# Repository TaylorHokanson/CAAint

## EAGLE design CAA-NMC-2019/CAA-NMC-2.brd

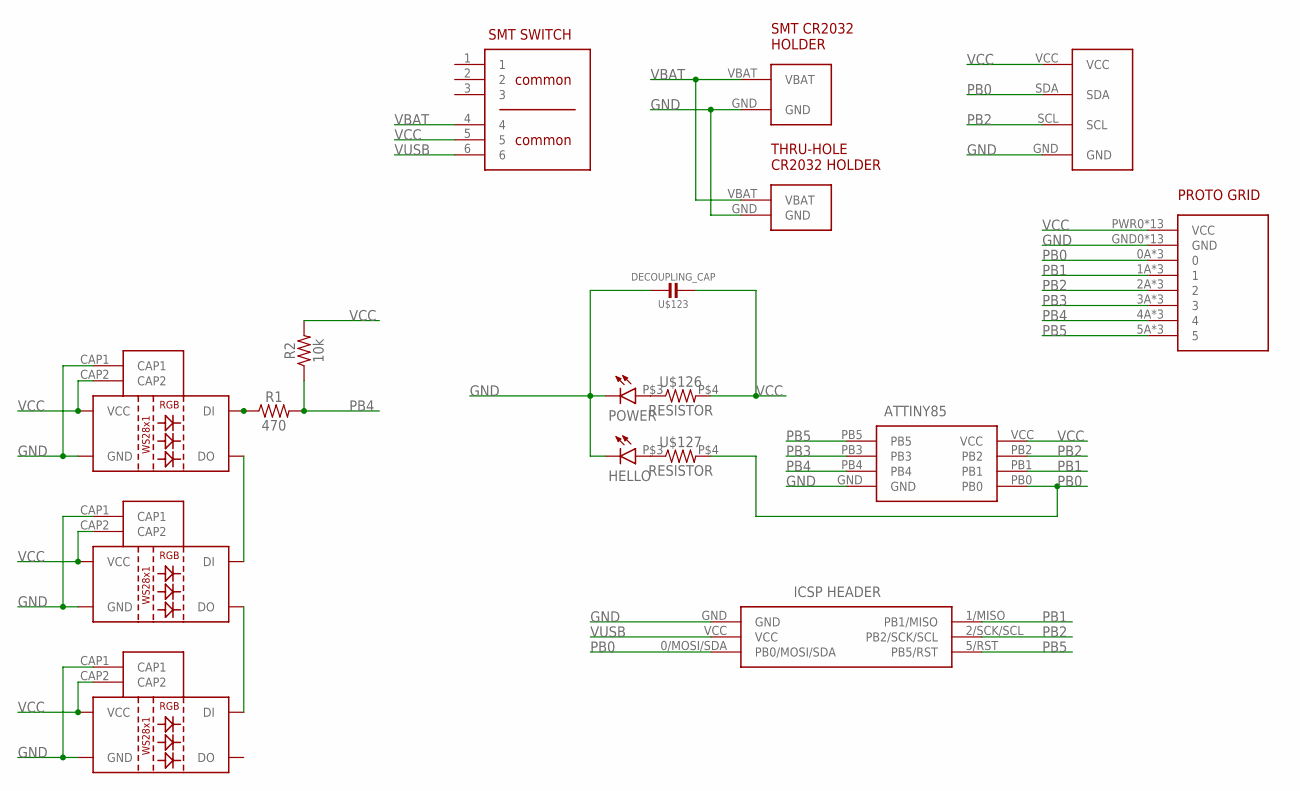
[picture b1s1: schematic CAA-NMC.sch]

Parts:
D1, D2, D3: WS2812B
HELLO: LED3MM
IC1: ATTINY85-20SU; SOT127P798X216-8N
J1: M20-9980346; HDRV6W64P254_2X3_762X508X868P
POWER: LED3MM
R1: 470; 0603
R2: 10k; 0603
U$1: PROTO
U$2: SMT-BATTERY-HOLDER; SMT-CR-HOLDER
U$3: THRU-CR-HOLDER
U$4: I2C-PADS
U$123: DECOUPLING_CAP
U$126, U$127: RESISTOR; AXIAL-0.3
U$145: SMT-SWITCH

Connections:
GND: D1.CAP1, D1.GND, D2.CAP1, D2.GND, D3.CAP1, D3.GND, HELLO.NEG, IC1.GND, J1.GND, POWER.NEG, U$1.GND0 (GND), U$1.GND1 (GND), U$1.GND2 (GND), U$1.GND3 (GND), U$1.GND4 (GND), U$1.GND5 (GND), U$1.GND6 (GND), U$1.GND7 (GND), U$1.GND8 (GND), U$1.GND9 (GND), U$1.GND10 (GND), U$1.GND11 (GND), U$1.GND12 (GND), U$2.GND, U$3.GND, U$4.GND, U$123.P$1 (1)
unnamed: POWER.POS, U$126.P$3 (1)
unnamed: HELLO.POS, U$127.P$3 (1)
unnamed: D1.DO, D2.DI
unnamed: D2.DO, D3.DI
unnamed: D1.DI, R1.1
PB0: IC1.PB0, J1.0/MOSI/SDA (PB0/MOSI/SDA), U$1.0A (0), U$1.0B (0), U$1.0C (0), U$4.SDA, U$127.P$4 (2)
PB1: IC1.PB1, J1.1/MISO (PB1/MISO), U$1.1A (1), U$1.1B (1), U$1.1C (1)
PB2: IC1.PB2, J1.2/SCK/SCL (PB2/SCK/SCL), U$1.2A (2), U$1.2B (2), U$1.2C (2), U$4.SCL
PB3: IC1.PB3, U$1.3A (3), U$1.3B (3), U$1.3C (3)
PB4: IC1.PB4, R1.2, R2.1, U$1.4A (4), U$1.4B (4), U$1.4C (4)
PB5: IC1.PB5, J1.5/RST (PB5/RST), U$1.5A (5), U$1.5B (5), U$1.5C (5)
VBAT: U$2.VBAT, U$3.VBAT, U$145.4
VCC: D1.CAP2, D1.VCC, D2.CAP2, D2.VCC, D3.CAP2, D3.VCC, IC1.VCC, R2.2, U$1.PWR0 (VCC), U$1.PWR1 (VCC), U$1.PWR2 (VCC), U$1.PWR3 (VCC), U$1.PWR4 (VCC), U$1.PWR5 (VCC), U$1.PWR6 (VCC), U$1.PWR7 (VCC), U$1.PWR8 (VCC), U$1.PWR9 (VCC), U$1.PWR10 (VCC), U$1.PWR11 (VCC), U$1.PWR12 (VCC), U$4.VCC, U$123.P$2 (2), U$126.P$4 (2), U$145.5
VUSB: J1.VCC, U$145.6

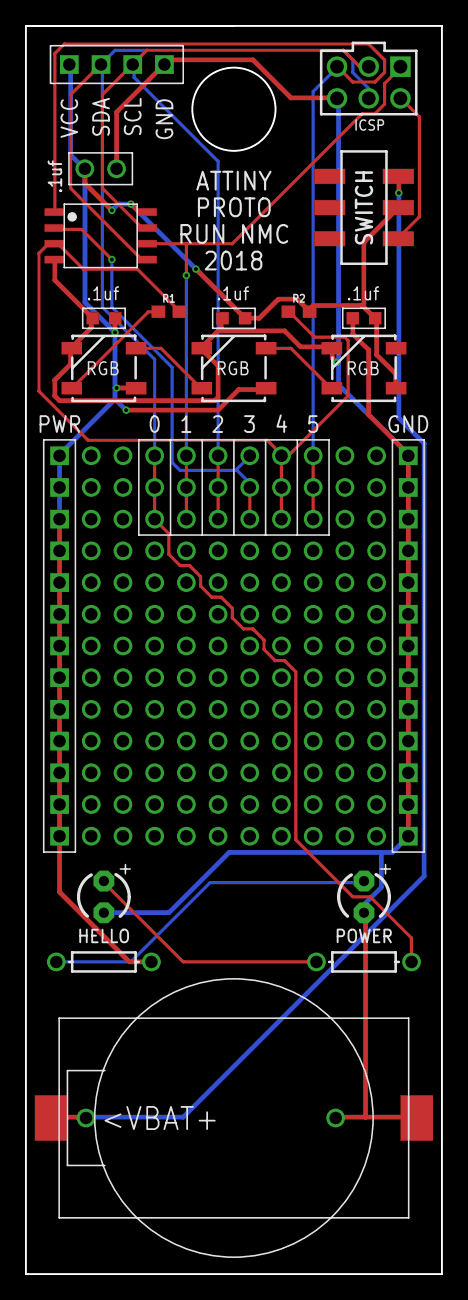
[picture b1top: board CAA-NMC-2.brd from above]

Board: 2 copper layers, 33.3 x 100.0 mm, 17 parts (0 on the bottom side), 15 nets.

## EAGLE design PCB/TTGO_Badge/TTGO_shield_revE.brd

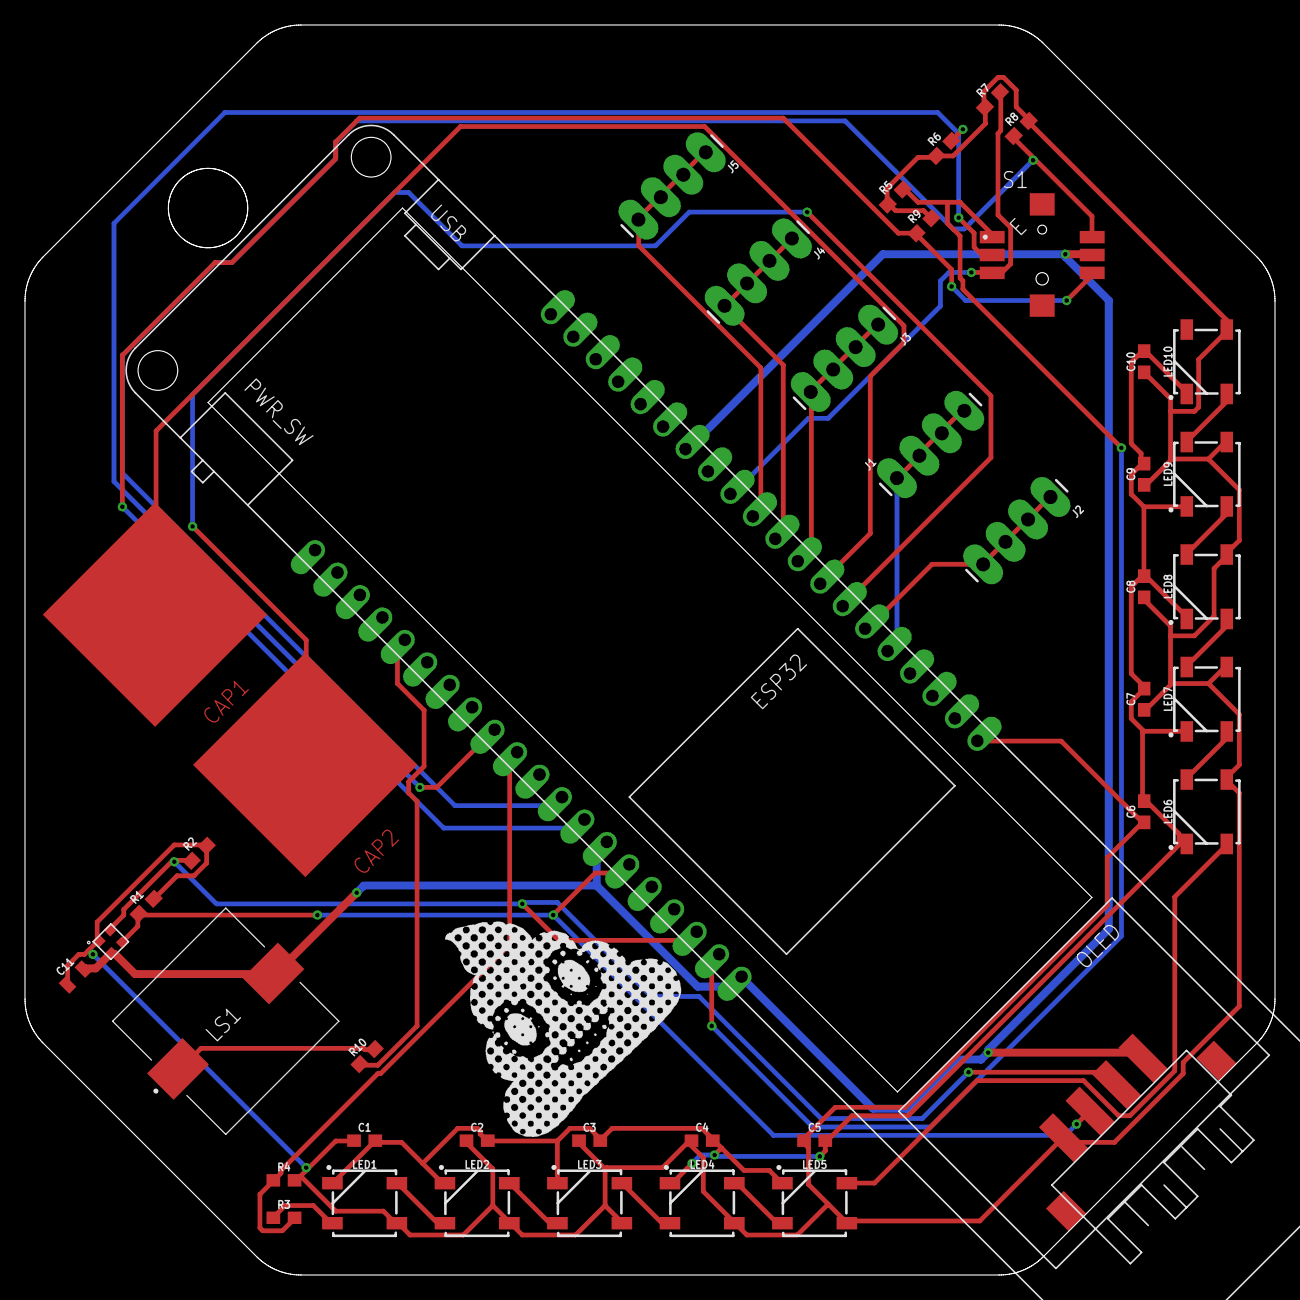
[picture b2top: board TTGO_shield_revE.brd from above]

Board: 2 copper layers, 100.0 x 100.0 mm, 43 parts (0 on the bottom side), 30 nets.

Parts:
C1, C2, C3, C4, C5, C6, C7, C8, C9, C10: 0.1uF; 0603
C11: 1.0uF; 0805
CAP1, CAP2: CAPSENSE_BUTTON
HEMA1: 10120045-400LF
J1, J2, J3, J4, J5: 1X04_LONGPADS
LED1, LED2, LED3, LED4, LED5, LED6, LED7, LED8, LED9, LED10: WS2812B
LS1: CT-1205H-SMT-TR; CT1205HSMTTR
LTSNS1: LTR-329ALS-01; CHIPLED-4
MAIN: TTGO-ESP32-OLED-18650
R1, R2: 4.7k; 0603
R3: 470; 0603
R4, R5, R6, R7, R8, R9: 10k; 0603
R10: 220; 0603
S1: JS1400BFQ

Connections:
15: MAIN.15, R10.1
25: J3.1, J3.2, J3.3, J3.4, MAIN.25
26: J4.1, J4.2, J4.3, J4.4, MAIN.26
27: J5.1, J5.2, J5.3, J5.4, MAIN.27
32: CAP2.1, MAIN.32
33: CAP1.1, MAIN.33
34: J1.1, J1.2, J1.3, J1.4, MAIN.34
35: J2.1, J2.2, J2.3, J2.4, MAIN.35
GND: C11.2, HEMA1.D, LS1.2, LTSNS1.2, MAIN.GND, MAIN.GND_2, MAIN.GND_3, S1.5
GND1: C1.2, C2.2, C3.2, C4.2, C5.2, C6.2, C7.2, C8.2, C9.2, C10.2, LED1.3, LED2.3, LED3.3, LED4.3, LED5.3, LED6.3, LED7.3, LED8.3, LED9.3, LED10.3
J-DOWN: MAIN.18, R8.1, S1.4
J-LEFT: MAIN.19, R9.1, S1.6
J-PRESS: MAIN.16, R6.2, S1.2
J-RIGHT: MAIN.23, R5.2, S1.1
J-UP: MAIN.14, R7.2, S1.3
unnamed: LED5.2, LED6.4
unnamed: LED6.2, LED7.4
unnamed: LED7.2, LED8.4
unnamed: LED8.2, LED9.4
unnamed: LED4.2, LED5.4
unnamed: LED9.2, LED10.4
unnamed: LS1.1, R10.2
unnamed: LED1.2, LED2.4
unnamed: LED2.2, LED3.4
unnamed: LED3.2, LED4.4
unnamed: LED1.4, R3.1
RGBLEDS: MAIN.17, R3.2, R4.1
SCL: HEMA1.C, LTSNS1.4, MAIN.22, R2.1
SDA: HEMA1.B, LTSNS1.3, MAIN.21, R1.1
VDD: C1.1, C2.1, C3.1, C4.1, C5.1, C6.1, C7.1, C8.1, C9.1, C10.1, C11.1, HEMA1.A, LED1.1, LED2.1, LED3.1, LED4.1, LED5.1, LED6.1, LED7.1, LED8.1, LED9.1, LED10.1, LTSNS1.1, MAIN.3.3V, R1.2, R2.2, R4.2, R5.1, R6.1, R7.1, R8.2, R9.2

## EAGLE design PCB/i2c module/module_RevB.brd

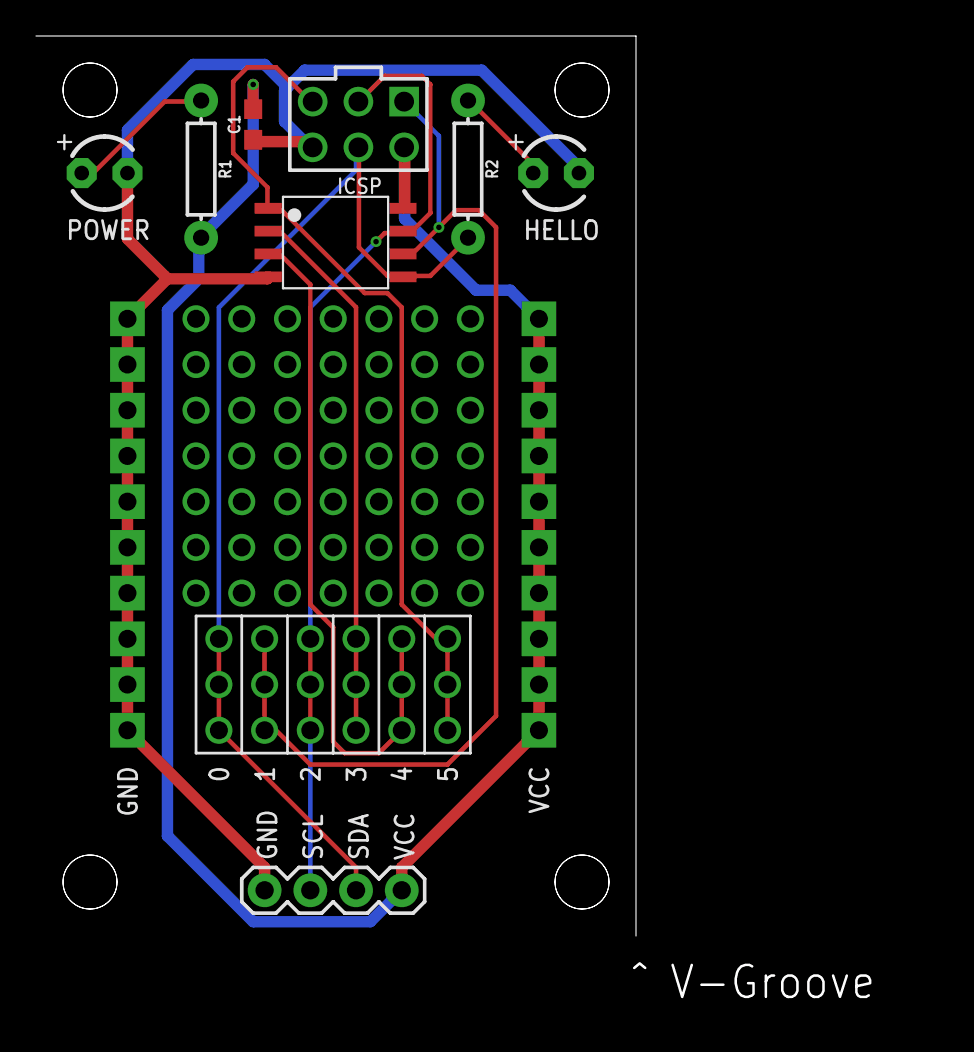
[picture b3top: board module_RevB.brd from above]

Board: 2 copper layers, 33.3 x 50.0 mm, 17 parts (0 on the bottom side), 10 nets.

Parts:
0, 1, 2, 3, 4, 5: 3X-PADS-CONNECTED; 3X-PADS
C1: 0.1uF; 0603
GND: 10X-PADS
HELLO: LED3MM
IC1: ATTINY85-20SU; SOT127P798X216-8N
J1: M20-9980346; HDRV6W64P254_2X3_762X508X868P
J2: 1X04
POWER: LED3MM
R1, R2: 220; AXIAL-0.3
U$2: 7X-PADS-NC
VCC: 10X-PADS

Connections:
GND: C1.1, GND.P$1, GND.P$2, GND.P$3, GND.P$4, GND.P$5, GND.P$6, GND.P$7, GND.P$8, GND.P$9, GND.P$10, HELLO.NEG, IC1.GND, J1.GND, J2.1, POWER.NEG
unnamed: POWER.POS, R1.P$1
unnamed: HELLO.POS, R2.P$1
PB0: 0.P$1, 0.P$2, 0.P$3, IC1.PB0, J1.0/MOSI/SDA, J2.3, R2.P$2
PB1: 1.P$1, 1.P$2, 1.P$3, IC1.PB1, J1.1/RST
PB2: 2.P$1, 2.P$2, 2.P$3, IC1.PB2, J1.2/SCK/SCL, J2.2
PB3: 3.P$1, 3.P$2, 3.P$3, IC1.PB3
PB4: 4.P$1, 4.P$2, 4.P$3, IC1.PB4
PB5: 5.P$1, 5.P$2, 5.P$3, IC1.PB5, J1.5/RST
VCC: C1.2, IC1.VCC, J1.VCC, J2.4, R1.P$2, VCC.P$1, VCC.P$2, VCC.P$3, VCC.P$4, VCC.P$5, VCC.P$6, VCC.P$7, VCC.P$8, VCC.P$9, VCC.P$10

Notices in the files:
parts and their libraries:
SparkFun-Resistors: Licensing: Creative Commons ShareAlike 4.0 International - https://creativecommons.org/licenses/by-sa/4.0
